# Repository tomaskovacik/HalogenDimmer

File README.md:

# HalogenDimmer
HW and SW for running halogen bulbs at 30% to act as daytime running lights.

# Overview
Module supports:
  - fade in at startup
  - fade out at shutdown
  - temporary disable with 3s delay (turn of DRL when turn signal is used, when using diodes more then one source of disable can used (low beams, turn signal... )
  - full on input for high beams, independent of microcontroler, used for light flasher and high beams
  - 30s turn off delay (comming home mode) - require permanent 12v supply and separete switched 12V connection to enable wire 
  
  # how-to connect module in headlight

  # pinout

  # video
  
  https://youtu.be/wNnqLfvapEo

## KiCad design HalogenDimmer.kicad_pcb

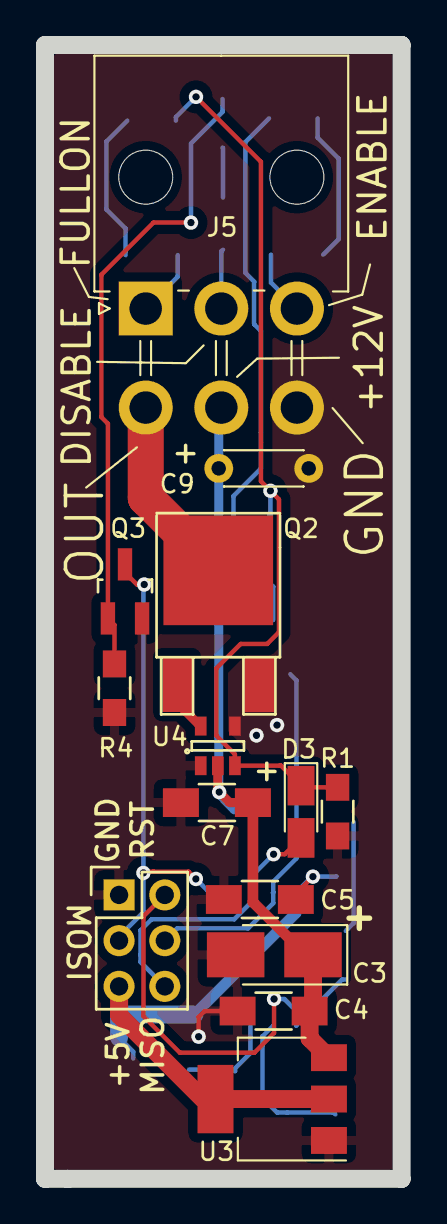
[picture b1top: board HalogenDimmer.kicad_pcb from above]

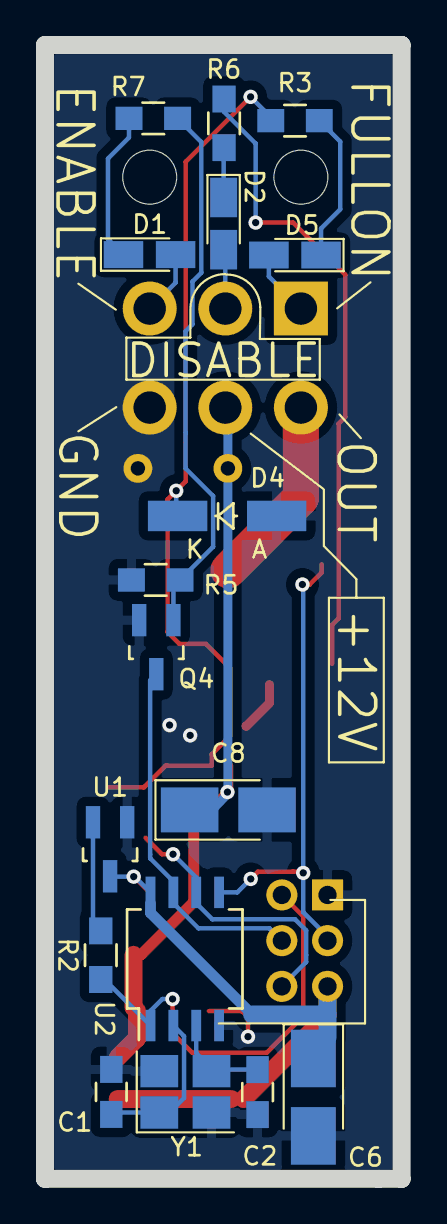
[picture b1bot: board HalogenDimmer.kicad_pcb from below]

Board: 2 copper layers, 19.8 x 63.0 mm, 31 parts (17 on the bottom side), 21 nets.

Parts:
C1, C2: 22p; C_0805_HandSoldering
C3: 22m/20V; CP_Tantalum_Case-B_EIA-3528-21_Hand
C4, C5, C7: 100n; C_1206_HandSoldering
C6: 47m/10V; CP_Tantalum_Case-B_EIA-3528-21_Hand
C8: 1m/10V; CP_Tantalum_Case-B_EIA-3528-21_Hand
C9: 1000m/16v; C_Disc_D4.3mm_W1.9mm_P5.00mm
D1, D2: NP; D_MicroMELF_Hadsoldering
D3, D5: 1n4148; D_MicroMELF_Hadsoldering
D4: 5V1; MiniMELF_Handsoldering
J1: SPI; Pin_Header_Straight_2x03
J5: INPUT_SIGNALS; Molex_MiniFit-JR-5569-06A2_2x03x4.20mm_Angled
Q2: IRL2905; TO-252-2Lead
Q3, Q4: BC817; SOT-23_Handsoldering
R1, R3, R4, R5: 1k; R_0805_HandSoldering
R2, R6, R7: 10k; R_0805_HandSoldering
U1: MAX809; SOT-23_Handsoldering
U2: ATtiny85-20SU; SO-8_5.3x6.2mm_Pitch1.27mm
U3: NCP1117LPST50T3G; SOT-223-3_TabPin2
U4: MCP1402; SOT-23-5
Y1: Crystal_GND24; Crystal_SMD_3225-4pin_3.2x2.5mm_HandSoldering

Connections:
+5V: C5.1, C6.1, J1.5, U1.3 (VCC), U2.8 (VCC), U3.2 (VO)
+12V: C3.1, C4.1, C7.1, C8.1, C9.1, J5.5, U3.3 (VI), U4.2 (Vdd)
/DISABLE: D2.2 (A), J5.2
/ENABLE: D1.2 (A), J5.3
/FULLON: D5.2 (A), J5.1
/MISO: D3.2 (A), J1.6, U2.6 (PB1)
/MOSI: J1.3, Q3.3 (C), U2.5 (AREF/PB0)
/OUT: J5.4, Q2.2 (D)
/PB2: J1.4, Q4.3 (C), U2.7 (PB2)
/RESET: J1.2, R2.1, U2.1 (~RESET~/PB5)
/XTAL1: C1.1, U2.2 (XTAL1/PB3), Y1.1
/XTAL2: C2.1, U2.3 (XTAL2/PB4), Y1.3
GND: C1.2, C2.2, C3.2, C4.2, C5.2, C6.2, C7.2, C8.2, C9.2, D4.2 (A), J1.1, J5.6, Q2.3 (S), Q3.2 (E), Q4.2 (E), R1.1, R4.2, R5.2, U1.1 (GND), U2.4 (GND), U3.1 (GND), U4.1 (GND), U4.4 (GND), Y1.2, Y1.4
unnamed: D1.1 (K), R7.2
unnamed: D2.1 (K), R6.2
unnamed: D3.1 (K), D4.1 (K), R1.2, R3.1, U4.3 (IN)
unnamed: D5.1 (K), R3.2
unnamed: Q2.1 (G), U4.5 (OUT)
unnamed: Q3.1 (B), R4.1, R6.1
unnamed: Q4.1 (B), R5.1, R7.1
unnamed: R2.2, U1.2 (RESET)

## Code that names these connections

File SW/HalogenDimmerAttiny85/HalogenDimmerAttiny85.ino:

// (c) kovo
//hallogen dimmer

/*
 * 3.7.2024 kovo: typos, cleanup commented out code 
 */

//timer1 @ 64Mhz
#include <avr/sleep.h>    // Sleep Modes
#include <avr/power.h>    // Power management

#define DELAY 50 // delay used in fade in, used to start DRL
#define DUTY 30 // duty cycle for DRL
#define OUT_PIN 1   //PB1 - output for PWM signal 
#define ONOFF_PIN 2    //PB2 - detecting if ON/OFFF state + wakeup from sleep - must be PB2 because INT0
#define DISABLE_PIN 0   //PB0 - detecting turnsignal, lowbeam etc to disable PWM high beam output
#define TURNSIGNAL_DELAY 5000 //safe delay to enable back DRL's if not turnsignal is present (or lowbeams...)
#define COMMING_HOME_DELAY 30000

enum state {
  OFF, // everything is off
  ON,// DRL ON
  SLEEP, //LOWPOWER MODE
  DISABLE, //LOW BEAMS ON,TURNSIGNAL ON, DRL OFF, NO SLEEP
  COMMING_HOME //30s delay before sleep
};


volatile uint8_t status = OFF;
volatile long disable_start_time;
volatile long offdelay_time;
volatile uint8_t set_duty = 0;

void go2sleep ()
{
  set_duty=0;
  analogWrite(OUT_PIN, set_duty);
  PCMSK  |= bit (PCINT2);  // want pin D4 / pin 3
  GIFR   |= bit (PCIF);    // clear any outstanding interrupts
  GIMSK  |= bit (PCIE);    // enable pin change interrupts
  set_sleep_mode(SLEEP_MODE_PWR_DOWN);
  ADCSRA = 0;            // turn off ADC
  power_all_disable();  // power off ADC, Timer 0 and 1, serial interface
  sleep_enable();
  sleep_cpu();
  sleep_disable();
  power_all_enable();    // power everything back on
  GIMSK  &= ~ (1 << PCIE); // enable pin change interrupts
  status = OFF;
}  // end of goToSleep

void DRL_ON() {
  for (set_duty = 0; set_duty < DUTY; set_duty++) {
    //while we are spinning on DRL, DISABLE pin is set (we start LOW beams of exmaple) 
    // so we cut turning on DRL 
    //and imidietly jump to turning them off = fade out
    if (!digitalRead(DISABLE_PIN))
    {
      delay(50);//debounce
      if (!digitalRead(DISABLE_PIN)) {
        disable_start_time = millis();
        status = DISABLE;
        return;
      }
    }
    analogWrite(OUT_PIN, set_duty);
    delay(DELAY); //DELAY=50ms, duty 30 => rump up is 1500ms aka 1.5s
  }
  //all good, we DRL is ON
  status = ON;
}

void DRL_OFF() {
  for (set_duty; set_duty > 0; set_duty--) {
    //do not checking for pin status, this rutine is used in more then one places
    //pin DISABLE change is handled in main loop
    analogWrite(OUT_PIN, set_duty);
    delay(DELAY); //DELAY=50ms, duty 30 => rump up is 1500ms aka 1.5s
  }
  //analogWrite(OUT_PIN, 0);//should not be needed....
  status = OFF;
}

void setup() {
  //  uncoment for 32kHz ouput
  //  TCCR1 &=~(1<<CS13);
  //  TCCR1 &=~(1<<CS12);
  //  TCCR1 &=~(1<<CS11);
  //  TCCR1 |=(1<<CS10);
  pinMode(DISABLE_PIN, INPUT_PULLUP);
  pinMode(ONOFF_PIN, INPUT_PULLUP);
  digitalWrite(OUT_PIN, LOW);
  pinMode(OUT_PIN, OUTPUT);
  digitalWrite(OUT_PIN, LOW);
}

void loop() {
  switch (status) {
    case OFF:
      //wakeded up, and goes straight to low beams = disable pin is low
      if (!digitalRead(ONOFF_PIN)) //HW inverted, using transistor 
        //we start drl and disable it in next run in main loop
        DRL_ON(); 
      else
        go2sleep();
      break;
    case ON:
      if (!digitalRead(DISABLE_PIN)) {
        delay(50);//debounce
        if (!digitalRead(DISABLE_PIN)) {
          status = DISABLE;
        }
      }
      if (digitalRead(ONOFF_PIN)) {
        delay(50);
        if (digitalRead(ONOFF_PIN)) {
          offdelay_time = millis() + 30000;
          while ((millis() < offdelay_time) && digitalRead(ONOFF_PIN)); //wait for 30s
          go2sleep();
        }
      }
      break;
    case SLEEP:
      //this should not happened, but in case, sleep:
      analogWrite(OUT_PIN, 0);
      go2sleep();
      break;
    case DISABLE:
      disable_start_time = millis();
      DRL_OFF();
      //loop for 3seconds if DISABLE pin is not set
      //otherwise loop forever
      while ((millis() - disable_start_time) < 3000) {
        if (!digitalRead(DISABLE_PIN)) {
          delay(50);//debounce
          if (!digitalRead(DISABLE_PIN)) {
            disable_start_time = millis();
          }
        }
      }
      break;

  }
}

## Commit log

2021-08-09 initSW
2021-08-09 ibom
2021-08-09 how_to_connect_picure
2021-08-10 pinout picture
2021-08-11 new pic of module
2023-04-11 change from low beams to parking/marking ligts
2023-04-11 typo
2023-04-11 HW changes
2024-07-03 clean up commentedout code
